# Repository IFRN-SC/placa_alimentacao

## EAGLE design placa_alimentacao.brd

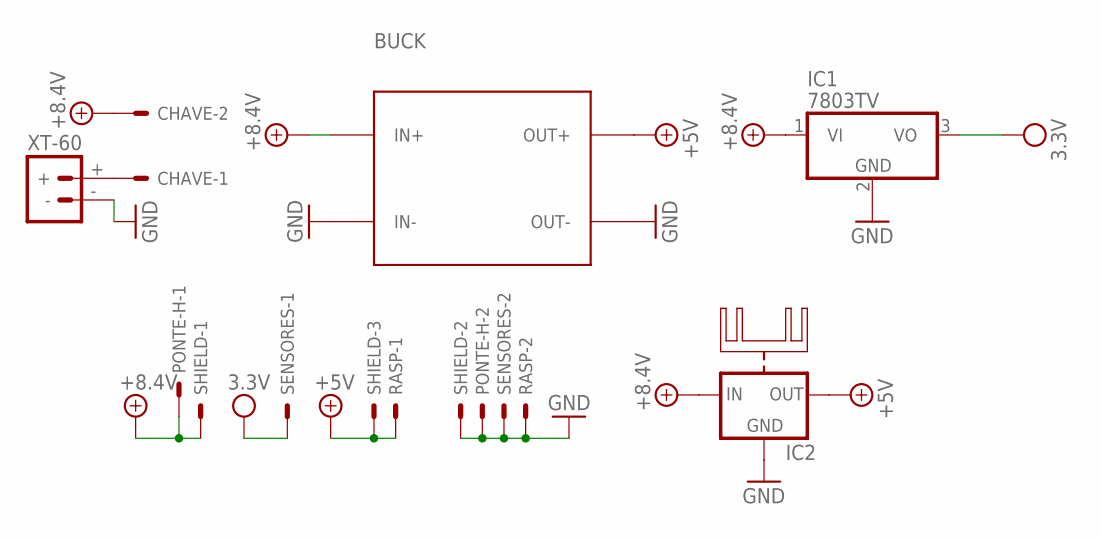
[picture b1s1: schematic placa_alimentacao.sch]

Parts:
BUCK: DC-DC-STEP-DOWN-LM2596
CHAVE: CONN_0227-2021; 6410-02
IC1: 7803TV; TO220V
IC2: 78XXH
PONTE-H: CONN_0227-2021; 6410-02
RASP: CONN_0227-2021; 6410-02
SENSORES: CONN_0227-2021; 6410-02
SHIELD: CONN_0327-2031; 6410-03
XT-60: BATTERY_CONNXT60; XT60

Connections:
+5V: BUCK.OUT+, IC2.OUT, RASP.1, SHIELD.3
+8V: BUCK.IN+, CHAVE.2, IC1.1 (VI), IC2.IN, PONTE-H.1, SHIELD.1
GND: BUCK.IN-, BUCK.OUT-, IC1.2 (GND), IC2.GND, PONTE-H.2, RASP.2, SENSORES.2, SHIELD.2, XT-60.-
unnamed: CHAVE.1, XT-60.+
VCC: IC1.3 (VO), SENSORES.1

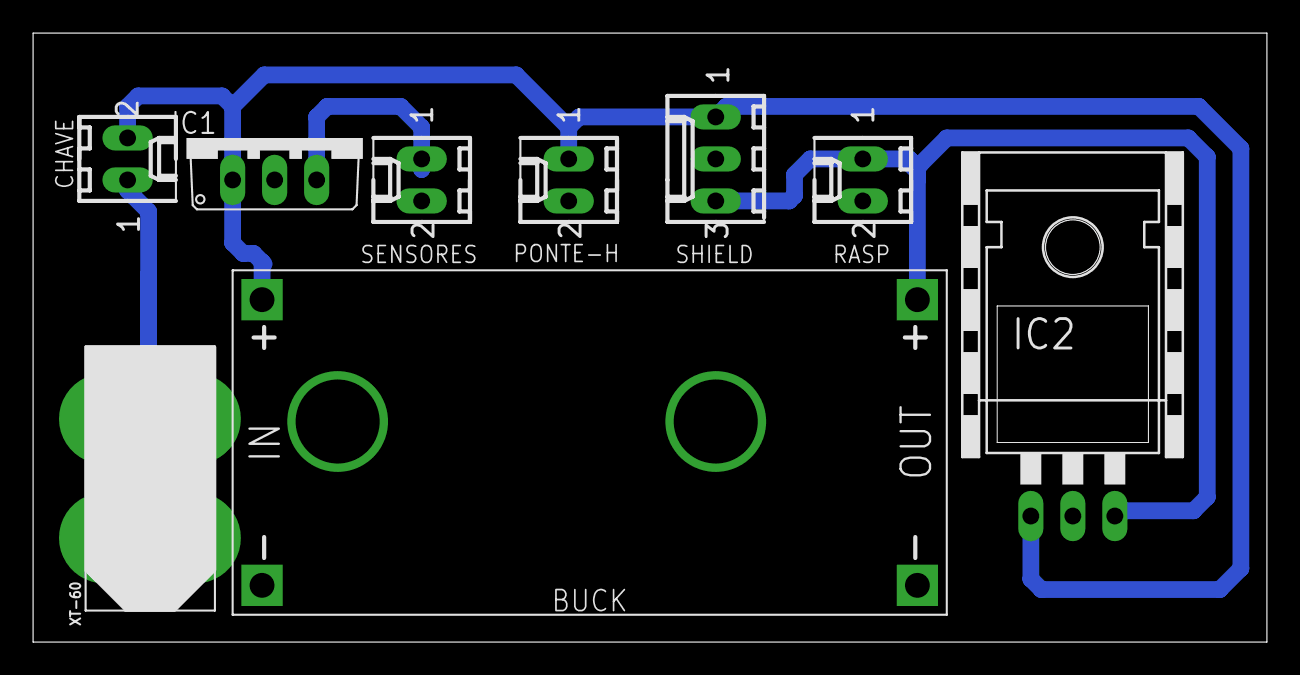
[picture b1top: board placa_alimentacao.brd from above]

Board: 2 copper layers, 74.6 x 36.8 mm, 9 parts (0 on the bottom side), 5 nets.

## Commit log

2018-07-02 Iniciação de placa de alimentação
2018-07-02 inicialização do gitignore
2018-07-02 Modificação do tamanho da placa
2018-07-02 Nova diminuição da placa.
2019-04-25 Adicionado regulador de tensão
2019-04-30 Erro tirado
    Schematic and board insconsistentes
2019-05-01 Texto adicionado
